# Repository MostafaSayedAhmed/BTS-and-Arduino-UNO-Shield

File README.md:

# BTS and Arduino Shield for Motor and Actuator Control

## Overview

This project is a custom-designed shield for Arduino, intended for controlling motors and actuators using the **BTS Linear Actuator Driver** and **A4988 Stepper Motor Driver**. It provides an interface to control different types of motors, including DC motors and stepper motors, and includes features to adjust sensitivity and control modes. This shield is well-suited for robotics, automation, and projects that require precise control of linear and rotational motion.

## Features

- **BTS Linear Actuator Driver**:
  - Capable of controlling linear actuators for various automation applications.
  - Supports PWM control for precise actuator positioning.
  - Provides GND, LPWM, RPWM, and VCC pins for easy connectivity.

- **DC Motor Driver**:
  - Designed to handle DC motors with configurable settings.
  - Control pins include GND, PWM, and VCC to ensure flexible power options.

- **A4988 Stepper Motor Driver**:
  - Allows precise step and direction control of stepper motors.
  - Supports microstepping for smoother motion control.
  - Includes pins for STEP and DIR signals, plus power (VCC and GND).

- **RC Mode Configuration**:
  - Includes selectable configurations for 1ms and 2ms pulse width signals.
  - Adjustable sensitivity settings for controlling motor or actuator response.
  - LED indicators to show signal status and activity.

- **Analog and Potentiometer Mode**:
  - Potentiometer inputs allow for manual control of the motor or actuator's position.
  - Voltage input mode supports 0-5V control, suitable for analog signal control systems.

## Control Settings

The shield offers several control options, configured via jumpers and potentiometers:

1. **RC Mode (1ms and 2ms Pulse Width)**:
   - Jumper settings enable selection between 1ms and 2ms pulse widths, commonly used in RC servo control applications.
   - Supports independent power supply to prevent interference with Arduino’s power supply.
   - Simple wiring with three connections: RC (signal), GND, and VCC (optional, only if needed).

2. **Voltage and Potentiometer Input Mode**:
   - This mode allows controlling the motor or actuator using analog voltage (0-5V) or a potentiometer.
   - Adjustable potentiometer inputs (10k, 50k, 100k) for manual tuning.
   - Ideal for applications where precise, hands-on control is required.

3. **Adjustable Sensitivity**:
   - Two potentiometers for adjusting the sensitivity range and rotation angle of the actuator or motor.
   - These allow fine-tuning to fit specific use cases, making the shield versatile for various control applications.

## Specifications

- **Dimensions**: 117.13 mm x 68.63 mm (fits standard Arduino form factor)
- **Input Voltage**: Supports 5V input for digital controls, 0-5V analog input for potentiometer control.
- **Compatibility**: Compatible with Arduino and other microcontroller boards with similar pin layouts.

## Setup and Usage

1. **Power Supply**:
   - Connect the DC power supply to the `DC POWER INPUT` terminals.
   - Ensure correct polarity when wiring, as reversing power input may damage the shield.

2. **Jumper Configuration**:
   - Use the jumpers to switch between different modes (RC Mode, Potentiometer Mode).
   - Set the desired pulse width or analog control mode as per your application.

3. **Connections**:
   - Connect your actuator or motor to the appropriate terminals (e.g., BTS Linear Actuator, DC Motor, Stepper Motor).
   - Use the Arduino’s digital or analog pins to control the actuator or motor based on the selected mode.

4. **Tuning and Adjustments**:
   - Use the potentiometers on the board to adjust the sensitivity and rotation angle range for optimal control response.
   - Refer to the LED indicators for feedback on control signals and operational status.

## Warnings

- **Power Input Polarity**: Ensure correct polarity when connecting the power supply. Incorrect wiring can cause permanent damage to the shield and connected components.
- **Independent Power for Servos**: When using RC Mode, provide an independent power supply for servos if necessary, as indicated in the documentation.

## Applications

This shield is suitable for applications requiring precise and configurable motor or actuator control, including:

- Robotics and automation systems
- Remote-controlled vehicles and drones
- Linear positioning systems
- Custom servo control setups

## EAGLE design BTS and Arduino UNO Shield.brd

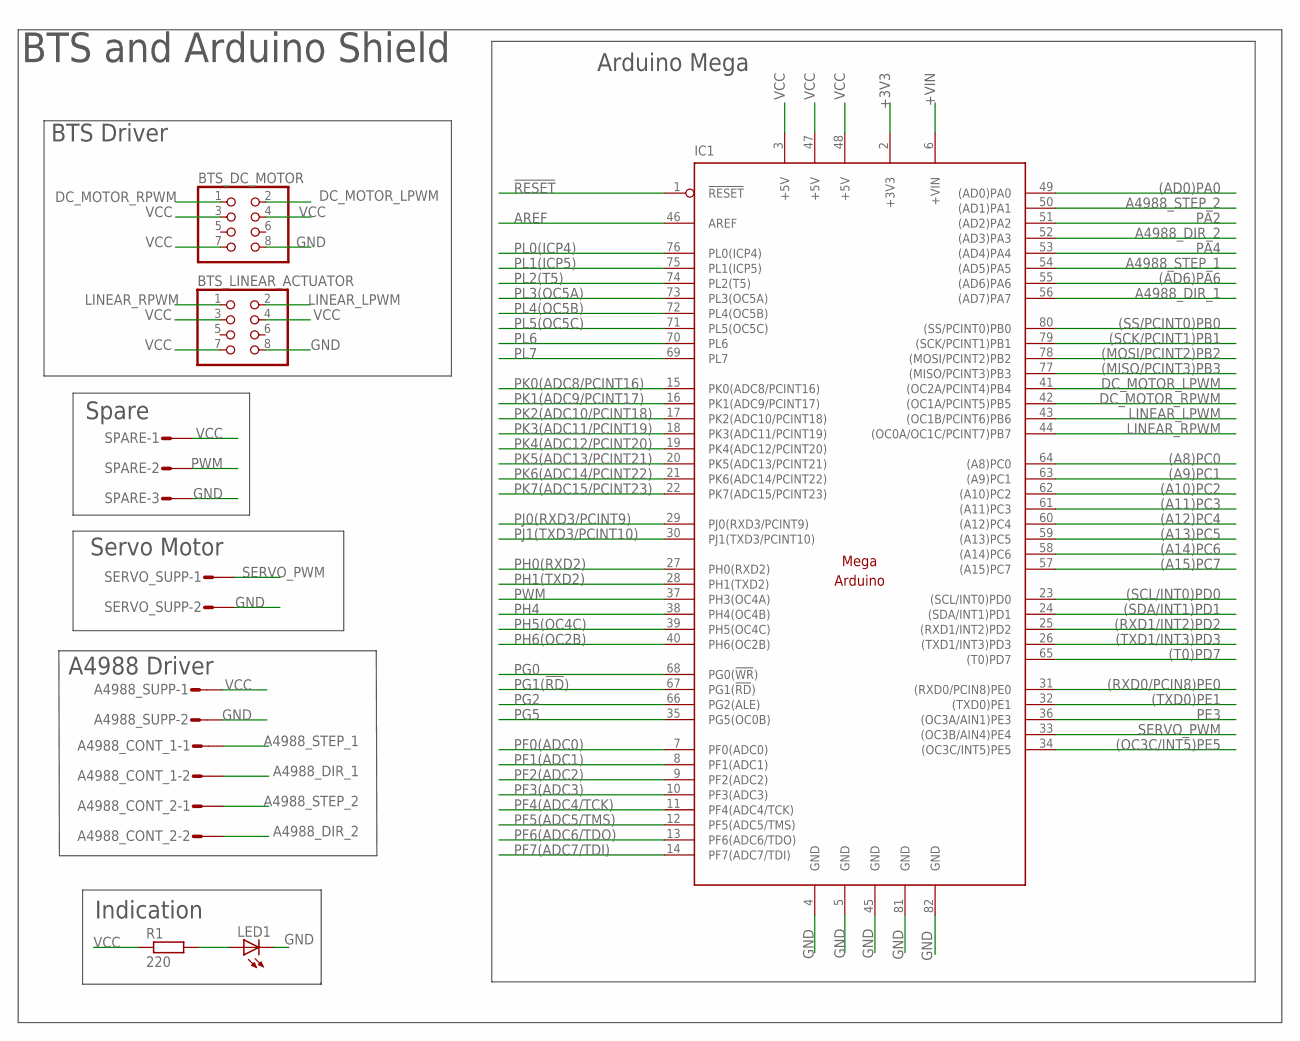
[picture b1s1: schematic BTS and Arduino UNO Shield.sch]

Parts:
A4988_CONT_1, A4988_CONT_2, A4988_SUPP: CON-AMP-MT_S02P
BTS_DC_MOTOR: PINHD-2X4; 2X04
BTS_LINEAR_ACTUATOR: PINHD-2X4; 2X04
IC1: MEGAARDUINO_1; MEGA_ARDUINO
LED1: LED_LED3MM
R1: 220; RCL_0204/7
SERVO_SUPP: CON-AMP-MT_S02P
SPARE: CON-AMP-MT_S03P

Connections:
!RESET: IC1.1 (!RESET)
(A8)PC0: IC1.64 ((A8)PC0)
(A9)PC1: IC1.63 ((A9)PC1)
(A10)PC2: IC1.62 ((A10)PC2)
(A11)PC3: IC1.61 ((A11)PC3)
(A12)PC4: IC1.60 ((A12)PC4)
(A13)PC5: IC1.59 ((A13)PC5)
(A14)PC6: IC1.58 ((A14)PC6)
(A15)PC7: IC1.57 ((A15)PC7)
(AD0)PA0: IC1.49 ((AD0)PA0)
(AD6)PA6: IC1.55 ((AD6)PA6)
(MISO/PCINT3)PB3: IC1.77 ((MISO/PCINT3)PB3)
(MOSI/PCINT2)PB2: IC1.78 ((MOSI/PCINT2)PB2)
(OC3C/INT5)PE5: IC1.34 ((OC3C/INT5)PE5)
(RXD0/PCIN8)PE0: IC1.31 ((RXD0/PCIN8)PE0)
(RXD1/INT2)PD2: IC1.25 ((RXD1/INT2)PD2)
(SCK/PCINT1)PB1: IC1.79 ((SCK/PCINT1)PB1)
(SCL/INT0)PD0: IC1.23 ((SCL/INT0)PD0)
(SDA/INT1)PD1: IC1.24 ((SDA/INT1)PD1)
(SS/PCINT0)PB0: IC1.80 ((SS/PCINT0)PB0)
(T0)PD7: IC1.65 ((T0)PD7)
(TXD0)PE1: IC1.32 ((TXD0)PE1)
(TXD1/INT3)PD3: IC1.26 ((TXD1/INT3)PD3)
+3V3: IC1.2 (+3V3)
+VIN: IC1.6 (+VIN)
A4988_DIR_1: A4988_CONT_1.2, IC1.56 ((AD7)PA7)
A4988_DIR_2: A4988_CONT_2.2, IC1.52 ((AD3)PA3)
A4988_STEP_1: A4988_CONT_1.1, IC1.54 ((AD5)PA5)
A4988_STEP_2: A4988_CONT_2.1, IC1.50 ((AD1)PA1)
AREF: IC1.46 (AREF)
DC_MOTOR_LPWM: BTS_DC_MOTOR.2, IC1.41 ((OC2A/PCINT4)PB4)
DC_MOTOR_RPWM: BTS_DC_MOTOR.1, IC1.42 ((OC1A/PCINT5)PB5)
GND: A4988_SUPP.2, BTS_DC_MOTOR.8, BTS_LINEAR_ACTUATOR.8, IC1.4 (GND), IC1.5 (GND), IC1.45 (GND), IC1.81 (GND), IC1.82 (GND), LED1.K (C), SERVO_SUPP.2, SPARE.3
LINEAR_LPWM: BTS_LINEAR_ACTUATOR.2, IC1.43 ((OC1B/PCINT6)PB6)
LINEAR_RPWM: BTS_LINEAR_ACTUATOR.1, IC1.44 ((OC0A/OC1C/PCINT7)PB7)
unnamed: LED1.A, R1.2
PA2: IC1.51 ((AD2)PA2)
PA4: IC1.53 ((AD4)PA4)
PE3: IC1.36 ((OC3A/AIN1)PE3)
PF0(ADC0): IC1.7 (PF0(ADC0))
PF1(ADC1): IC1.8 (PF1(ADC1))
PF2(ADC2): IC1.9 (PF2(ADC2))
PF3(ADC3): IC1.10 (PF3(ADC3))
PF4(ADC4/TCK): IC1.11 (PF4(ADC4/TCK))
PF5(ADC5/TMS): IC1.12 (PF5(ADC5/TMS))
PF6(ADC6/TDO): IC1.13 (PF6(ADC6/TDO))
PF7(ADC7/TDI): IC1.14 (PF7(ADC7/TDI))
PG0: IC1.68 (PG0(!WR!))
PG1(!RD!): IC1.67 (PG1(!RD!))
PG2: IC1.66 (PG2(ALE))
PG5: IC1.35 (PG5(OC0B))
PH0(RXD2): IC1.27 (PH0(RXD2))
PH1(TXD2): IC1.28 (PH1(TXD2))
PH4: IC1.38 (PH4(OC4B))
PH5(OC4C): IC1.39 (PH5(OC4C))
PH6(OC2B): IC1.40 (PH6(OC2B))
PJ0(RXD3/PCINT9): IC1.29 (PJ0(RXD3/PCINT9))
PJ1(TXD3/PCINT10): IC1.30 (PJ1(TXD3/PCINT10))
PK0(ADC8/PCINT16): IC1.15 (PK0(ADC8/PCINT16))
PK1(ADC9/PCINT17): IC1.16 (PK1(ADC9/PCINT17))
PK2(ADC10/PCINT18): IC1.17 (PK2(ADC10/PCINT18))
PK3(ADC11/PCINT19): IC1.18 (PK3(ADC11/PCINT19))
PK4(ADC12/PCINT20): IC1.19 (PK4(ADC12/PCINT20))
PK5(ADC13/PCINT21): IC1.20 (PK5(ADC13/PCINT21))
PK6(ADC14/PCINT22): IC1.21 (PK6(ADC14/PCINT22))
PK7(ADC15/PCINT23): IC1.22 (PK7(ADC15/PCINT23))
PL0(ICP4): IC1.76 (PL0(ICP4))
PL1(ICP5): IC1.75 (PL1(ICP5))
PL2(T5): IC1.74 (PL2(T5))
PL3(OC5A): IC1.73 (PL3(OC5A))
PL4(OC5B): IC1.72 (PL4(OC5B))
PL5(OC5C): IC1.71 (PL5(OC5C))
PL6: IC1.70 (PL6)
PL7: IC1.69 (PL7)
PWM: IC1.37 (PH3(OC4A)), SPARE.2
SERVO_PWM: IC1.33 ((OC3B/AIN4)PE4), SERVO_SUPP.1
VCC: A4988_SUPP.1, BTS_DC_MOTOR.3, BTS_DC_MOTOR.4, BTS_DC_MOTOR.7, BTS_LINEAR_ACTUATOR.3, BTS_LINEAR_ACTUATOR.4, BTS_LINEAR_ACTUATOR.7, IC1.3 (+5V), IC1.47 (+5V), IC1.48 (+5V), R1.1, SPARE.1

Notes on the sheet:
BTS and Arduino Shield
Indication
A4988 Driver
Servo Motor
Spare
BTS Driver
Arduino Mega

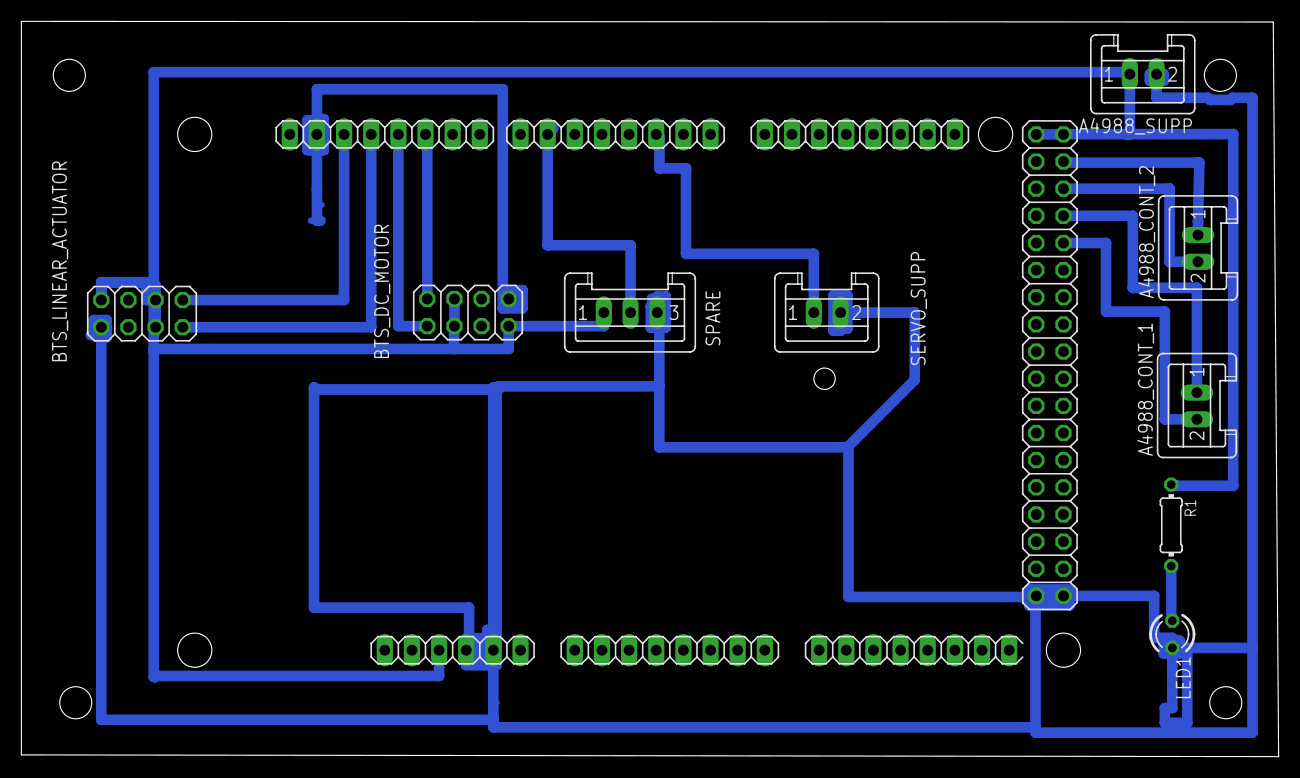
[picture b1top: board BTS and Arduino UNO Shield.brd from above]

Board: 2 copper layers, 117.6 x 68.8 mm, 10 parts (0 on the bottom side), 13 nets.
